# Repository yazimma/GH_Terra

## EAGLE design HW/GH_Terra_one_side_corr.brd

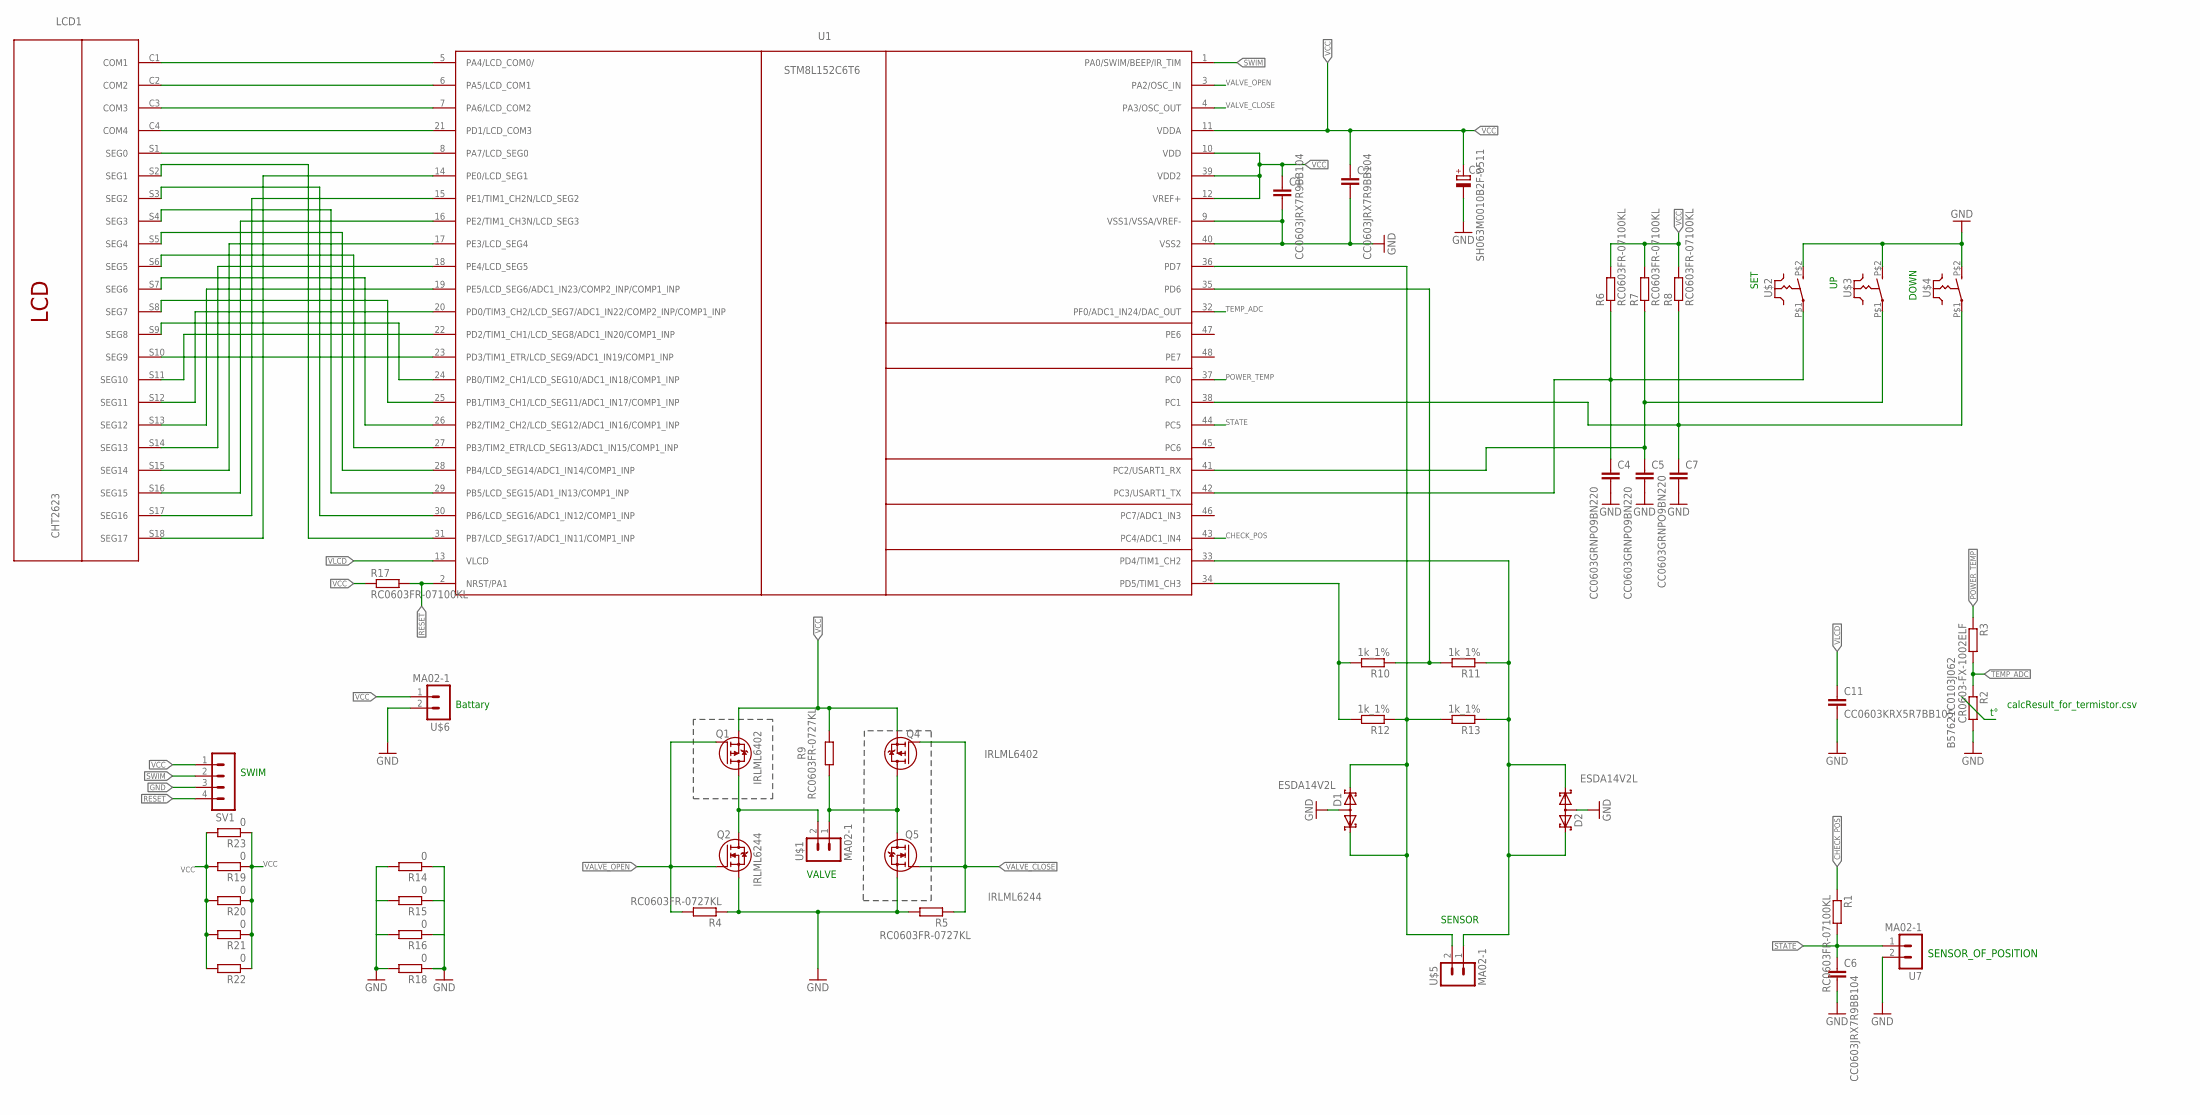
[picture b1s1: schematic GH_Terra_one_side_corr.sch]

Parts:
C1, C2, C6: CC0603JRX7R9BB104; C0603_IPC
C3: SH063M0010B2F-0511; SANYO-OSCON_C6
C4, C5, C7: CC0603GRNPO9BN220; C0603_IPC
C11: CC0603KRX5R7BB105; C0603_IPC
D1, D2: ESDA14V2L; SOT23
LCD1: CHT2623
Q1, Q4: IRLML6402; SOT23
Q2, Q5: IRLML6244; SOT23
R1, R6, R7, R8, R17: RC0603FR-07100KL; R0603_IPC
R2: B57621C0103J062; R1206
R3: CR0603-FX-1002ELF; R0603_IPC
R4, R5, R9: RC0603FR-0727KL; R0603_IPC
R10, R11, R12, R13: 1k_1%; R0603_IPC
R14, R15, R16, R18, R19, R20, R21, R22, R23: 0; R0603_IPC
SV1: MA04-1
U1: STM8L152C6T6; LQFP48
U7: MA02-1
U$1, U$5, U$6: MA02-1
U$2, U$3, U$4: RK_4X3; RK_3X4

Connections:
CHECK_POS: R1.1, U1.43 (PC4/ADC1_IN4)
GND: C1.2, C2.2, C3.-, C4.2, C5.2, C6.2, C7.2, C11.2, D1.3 (AA), D2.3 (AA), Q2.2 (S), Q5.2 (S), R2.2, R4.1, R5.2, R14.1, R14.2, R15.1, R15.2, R16.1, R16.2, R18.1, R18.2, SV1.3, U1.9 (VSS1/VSSA/VREF-), U1.40 (VSS2), U7.2, U$2.P$2 (S), U$3.P$2 (S), U$4.P$2 (S), U$6.2
unnamed: LCD1.C1 (COM1), U1.5 (PA4/LCD_COM0/)
unnamed: Q1.3 (D), Q2.3 (D), U$1.2
unnamed: Q4.3 (D), Q5.3 (D), R9.2, U$1.1
unnamed: LCD1.C2 (COM2), U1.6 (PA5/LCD_COM1)
unnamed: LCD1.C3 (COM3), U1.7 (PA6/LCD_COM2)
unnamed: LCD1.C4 (COM4), U1.21 (PD1/LCD_COM3)
unnamed: LCD1.S1 (SEG0), U1.8 (PA7/LCD_SEG0)
unnamed: LCD1.S17 (SEG16), U1.15 (PE1/TIM1_CH2N/LCD_SEG2)
unnamed: LCD1.S16 (SEG15), U1.16 (PE2/TIM1_CH3N/LCD_SEG3)
unnamed: LCD1.S15 (SEG14), U1.17 (PE3/LCD_SEG4)
unnamed: LCD1.S14 (SEG13), U1.18 (PE4/LCD_SEG5)
unnamed: LCD1.S13 (SEG12), U1.19 (PE5/LCD_SEG6/ADC1_IN23/COMP2_INP/COMP1_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)
unnamed: LCD1.S12 (SEG11), U1.20 (PD0/TIM3_CH2/LCD_SEG7/ADC1_IN22/COMP2_I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)
unnamed: LCD1.S11 (SEG10), U1.22 (PD2/TIM1_CH1/LCD_SEG8/ADC1_IN20/COMP1_I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)
unnamed: LCD1.S10 (SEG9), U1.23 (PD3/TIM1_ETR/LCD_SEG9/ADC1_IN19/COMP1_I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)
unnamed: LCD1.S9 (SEG8), U1.24 (PB0/TIM2_CH1/LCD_SEG10/ADC1_IN18/COMP1_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)
unnamed: LCD1.S8 (SEG7), U1.25 (PB1/TIM3_CH1/LCD_SEG11/ADC1_IN17/COMP1_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)
unnamed: LCD1.S7 (SEG6), U1.26 (PB2/TIM2_CH2/LCD_SEG12/ADC1_IN16/COMP1_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)
unnamed: LCD1.S6 (SEG5), U1.27 (PB3/TIM2_ETR/LCD_SEG13/ADC1_IN15/COMP1_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)
unnamed: LCD1.S5 (SEG4), U1.28 (PB4/LCD_SEG14/ADC1_IN14/COMP1_INP)
unnamed: LCD1.S4 (SEG3), U1.29 (PB5/LCD_SEG15/AD1_IN13/COMP1_INP)
unnamed: LCD1.S3 (SEG2), U1.30 (PB6/LCD_SEG16/ADC1_IN12/COMP1_INP)
unnamed: LCD1.S2 (SEG1), U1.31 (PB7/LCD_SEG17/ADC1_IN11/COMP1_INP)
unnamed: LCD1.S18 (SEG17), U1.14 (PE0/LCD_SEG1)
unnamed: D2.1 (K1), D2.2 (K2), R11.1, R13.1, U1.33 (PD4/TIM1_CH2), U$5.1
unnamed: R10.2, R12.2, U1.34 (PD5/TIM1_CH3)
unnamed: C4.1, R6.1, U1.42 (PC3/USART1_TX), U$2.P$1
unnamed: C5.1, R7.1, U1.41 (PC2/USART1_RX), U$3.P$1
unnamed: C7.1, R8.1, U1.38 (PC1), U$4.P$1
POWER_TEMP: R3.1, U1.37 (PC0)
RESET: R17.2, SV1.4, U1.2 (NRST/PA1)
STATE: C6.1, R1.2, U1.44 (PC5), U7.1
SWIM: SV1.2, U1.1 (PA0/SWIM/BEEP/IR_TIM)
TEMP_ADC: R2.1, R3.2, U1.32 (PF0/ADC1_IN24/DAC_OUT)
VALVE_CLOSE: Q4.1 (G), Q5.1 (G), R5.1, U1.4 (PA3/OSC_OUT)
VALVE_OPEN: Q1.1 (G), Q2.1 (G), R4.2, U1.3 (PA2/OSC_IN)
VCC: C1.1, C2.1, C3.+, Q1.2 (S), Q4.2 (S), R6.2, R7.2, R8.2, R9.1, R17.1, R19.1, R19.2, R20.1, R20.2, R21.1, R21.2, R22.1, R22.2, R23.1, R23.2, SV1.1, U1.10 (VDD), U1.11 (VDDA), U1.12 (VREF+), U1.39 (VDD2), U$6.1
VLCD: C11.1, U1.13 (VLCD)
VREF: R10.1, R11.2, U1.35 (PD6)
VREF1: D1.1 (K1), D1.2 (K2), R12.1, R13.2, U1.36 (PD7), U$5.2

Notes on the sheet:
calcResult_for_termistor.csv
Battary
SWIM
VALVE
SENSOR
SET
DOWN
SENSOR_OF_POSITION

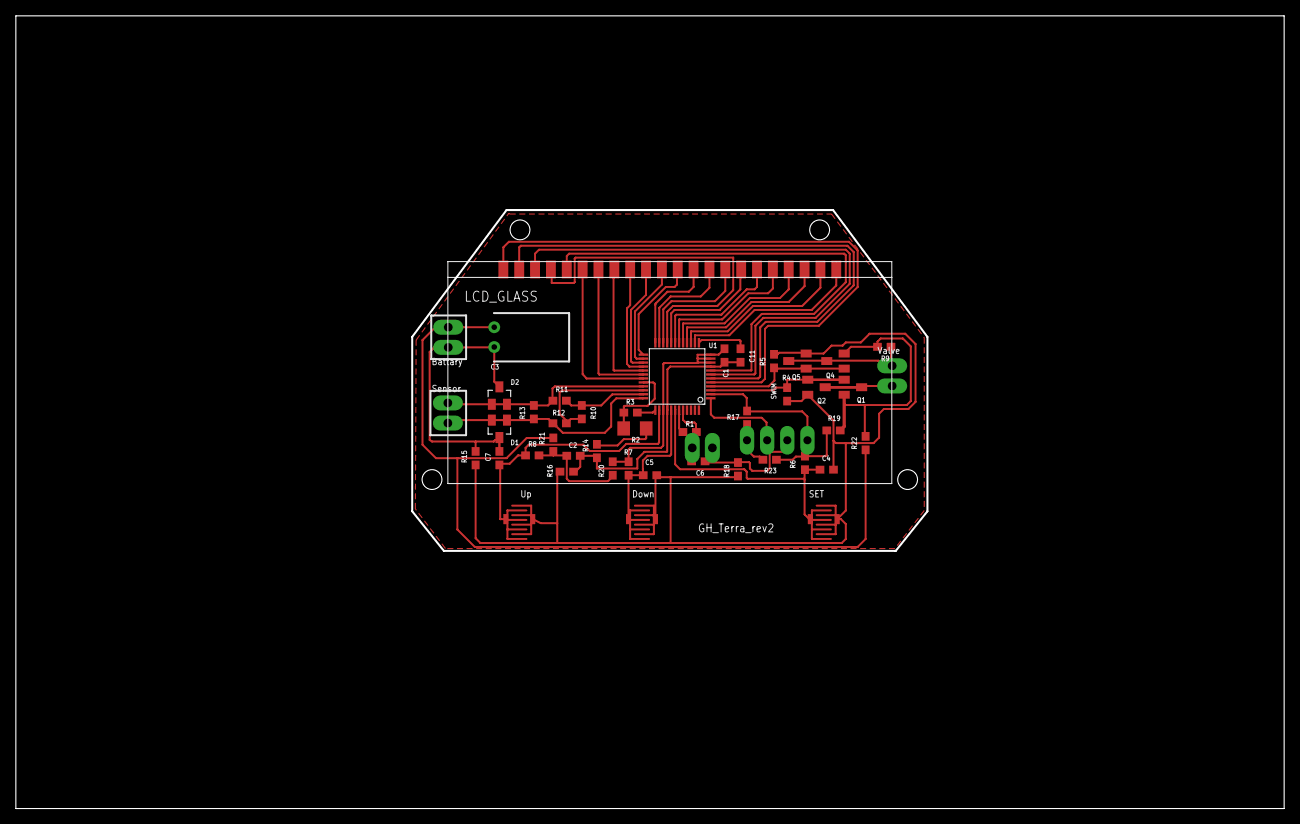
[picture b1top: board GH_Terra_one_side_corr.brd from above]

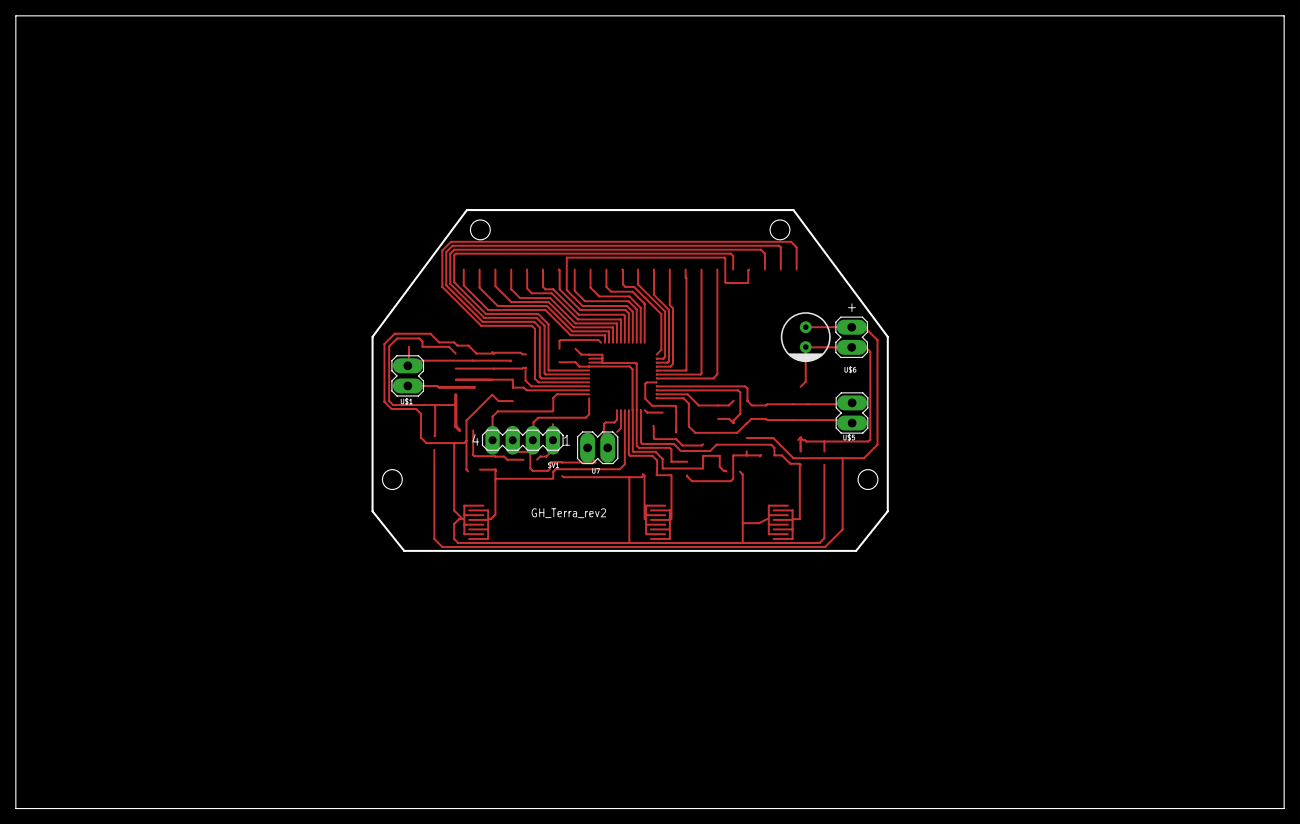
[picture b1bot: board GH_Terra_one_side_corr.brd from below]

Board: 2 copper layers, 160.0 x 100.0 mm, 47 parts (6 on the bottom side), 42 nets.

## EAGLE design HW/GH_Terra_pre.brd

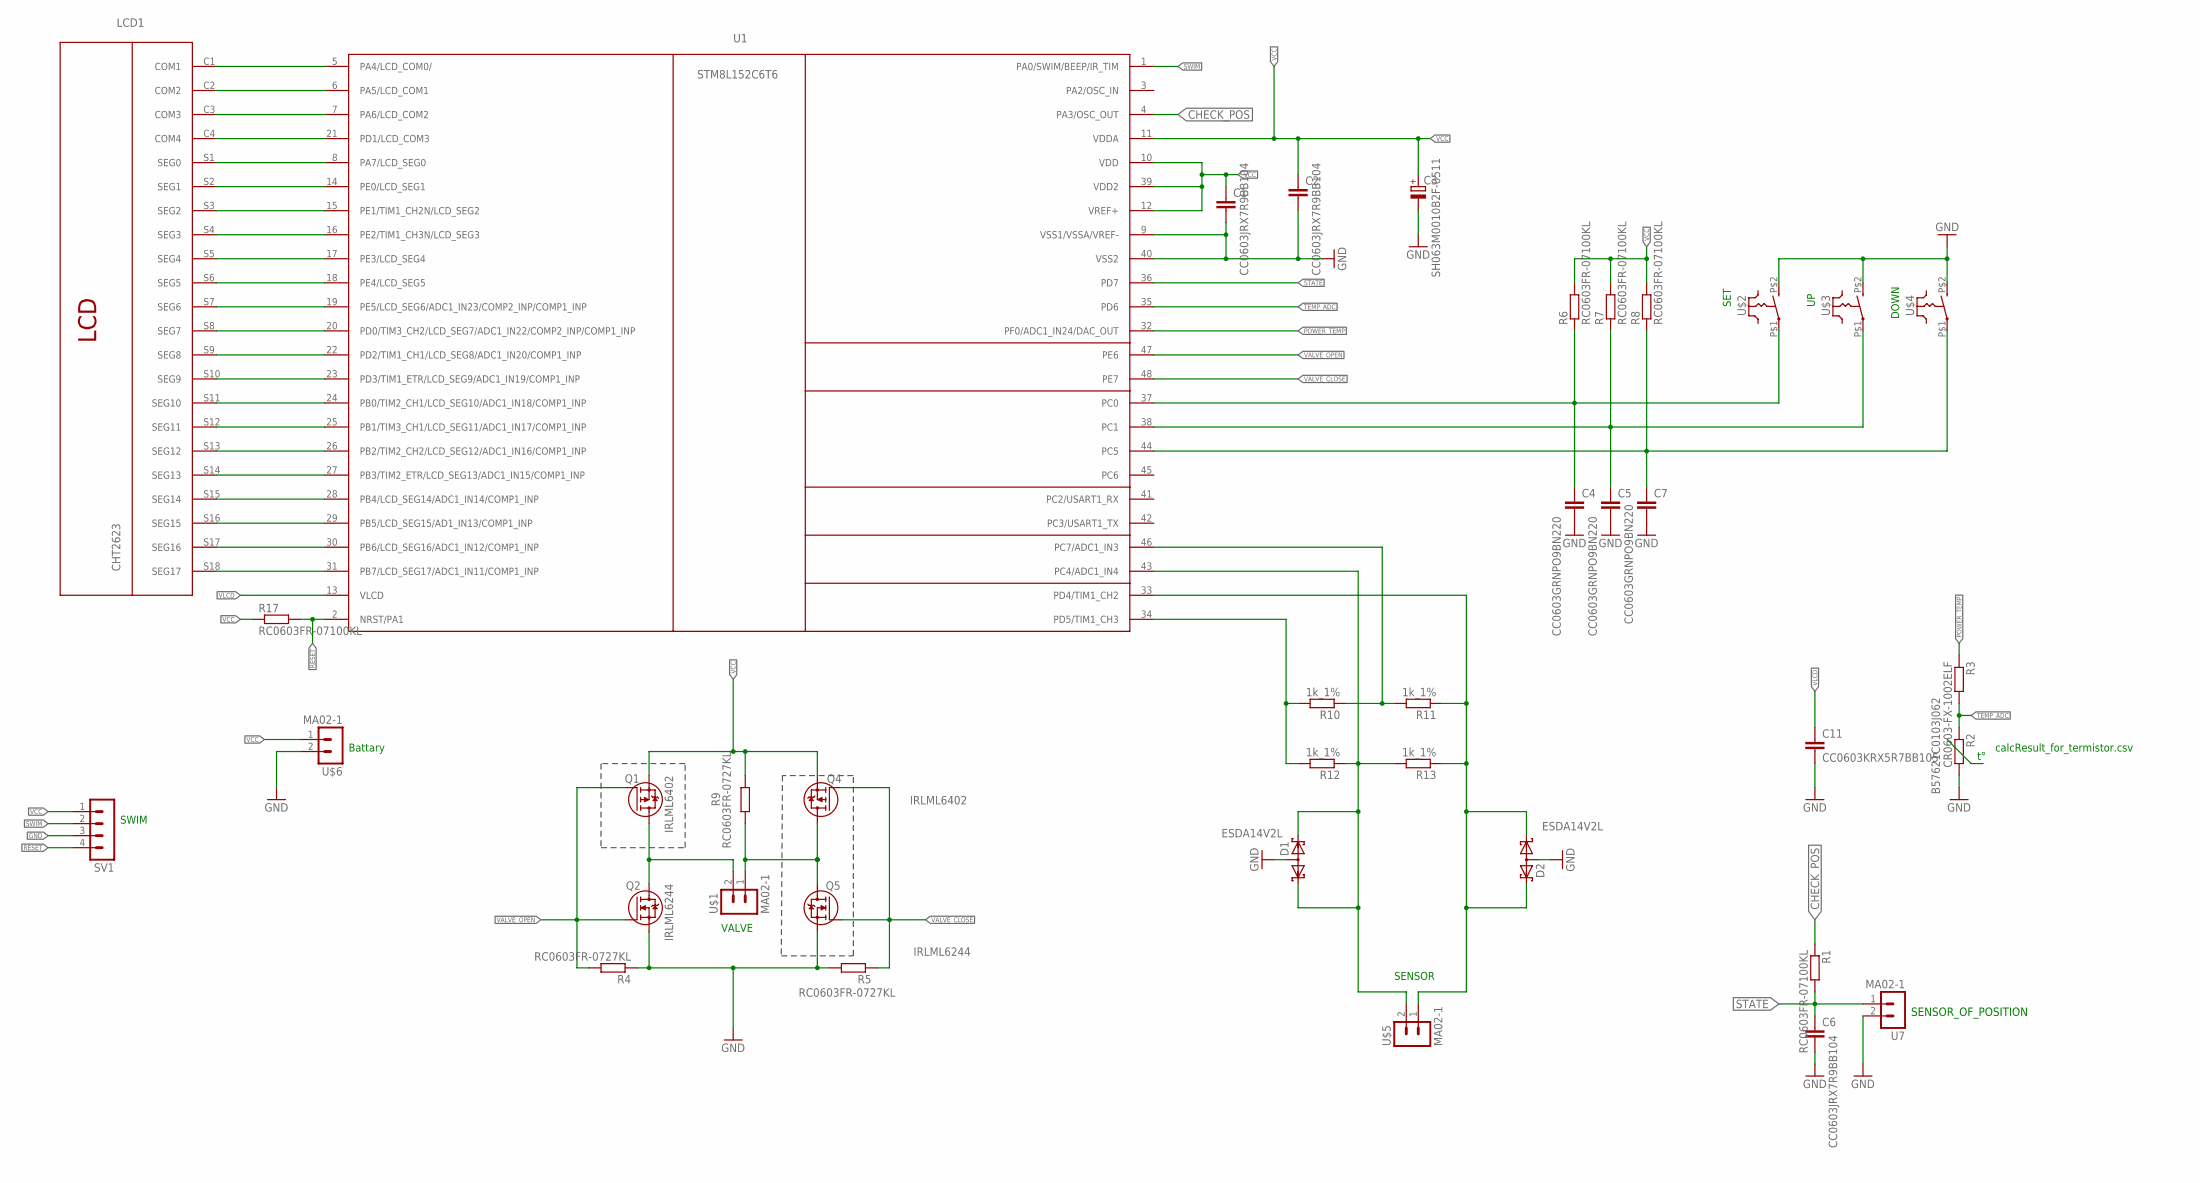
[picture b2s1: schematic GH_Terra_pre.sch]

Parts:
C1, C2, C6: CC0603JRX7R9BB104; C0603_IPC
C3: SH063M0010B2F-0511; SANYO-OSCON_C6
C4, C5, C7: CC0603GRNPO9BN220; C0603_IPC
C11: CC0603KRX5R7BB105; C0603_IPC
D1, D2: ESDA14V2L; SOT23
LCD1: CHT2623
Q1, Q4: IRLML6402; SOT23
Q2, Q5: IRLML6244; SOT23
R1, R6, R7, R8, R17: RC0603FR-07100KL; R0603_IPC
R2: B57621C0103J062; R1206
R3: CR0603-FX-1002ELF; R0603_IPC
R4, R5, R9: RC0603FR-0727KL; R0603_IPC
R10, R11, R12, R13: 1k_1%; R0603_IPC
SV1: MA04-1
U1: STM8L152C6T6; LQFP48
U7: MA02-1
U$1, U$5, U$6: MA02-1
U$2, U$3, U$4: RK_4X3; RK_3X4

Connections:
CHECK_POS: R1.1, U1.4 (PA3/OSC_OUT)
GND: C1.2, C2.2, C3.-, C4.2, C5.2, C6.2, C7.2, C11.2, D1.3 (AA), D2.3 (AA), Q2.2 (S), Q5.2 (S), R2.2, R4.1, R5.2, SV1.3, U1.9 (VSS1/VSSA/VREF-), U1.40 (VSS2), U7.2, U$2.P$2 (S), U$3.P$2 (S), U$4.P$2 (S), U$6.2
unnamed: Q1.3 (D), Q2.3 (D), U$1.2
unnamed: Q4.3 (D), Q5.3 (D), R9.2, U$1.1
unnamed: LCD1.C1 (COM1), U1.5 (PA4/LCD_COM0/)
unnamed: LCD1.C2 (COM2), U1.6 (PA5/LCD_COM1)
unnamed: LCD1.C3 (COM3), U1.7 (PA6/LCD_COM2)
unnamed: LCD1.C4 (COM4), U1.21 (PD1/LCD_COM3)
unnamed: LCD1.S1 (SEG0), U1.8 (PA7/LCD_SEG0)
unnamed: LCD1.S2 (SEG1), U1.14 (PE0/LCD_SEG1)
unnamed: LCD1.S3 (SEG2), U1.15 (PE1/TIM1_CH2N/LCD_SEG2)
unnamed: LCD1.S4 (SEG3), U1.16 (PE2/TIM1_CH3N/LCD_SEG3)
unnamed: LCD1.S5 (SEG4), U1.17 (PE3/LCD_SEG4)
unnamed: LCD1.S6 (SEG5), U1.18 (PE4/LCD_SEG5)
unnamed: LCD1.S7 (SEG6), U1.19 (PE5/LCD_SEG6/ADC1_IN23/COMP2_INP/COMP1_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)
unnamed: LCD1.S8 (SEG7), U1.20 (PD0/TIM3_CH2/LCD_SEG7/ADC1_IN22/COMP2_I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)
unnamed: LCD1.S9 (SEG8), U1.22 (PD2/TIM1_CH1/LCD_SEG8/ADC1_IN20/COMP1_I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)
unnamed: LCD1.S10 (SEG9), U1.23 (PD3/TIM1_ETR/LCD_SEG9/ADC1_IN19/COMP1_I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)
unnamed: LCD1.S11 (SEG10), U1.24 (PB0/TIM2_CH1/LCD_SEG10/ADC1_IN18/COMP1_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)
unnamed: LCD1.S12 (SEG11), U1.25 (PB1/TIM3_CH1/LCD_SEG11/ADC1_IN17/COMP1_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)
unnamed: LCD1.S13 (SEG12), U1.26 (PB2/TIM2_CH2/LCD_SEG12/ADC1_IN16/COMP1_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)
unnamed: LCD1.S14 (SEG13), U1.27 (PB3/TIM2_ETR/LCD_SEG13/ADC1_IN15/COMP1_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)
unnamed: LCD1.S15 (SEG14), U1.28 (PB4/LCD_SEG14/ADC1_IN14/COMP1_INP)
unnamed: LCD1.S16 (SEG15), U1.29 (PB5/LCD_SEG15/AD1_IN13/COMP1_INP)
unnamed: D2.1 (K1), D2.2 (K2), R11.1, R13.1, U1.33 (PD4/TIM1_CH2), U$5.1
unnamed: R10.2, R12.2, U1.34 (PD5/TIM1_CH3)
unnamed: LCD1.S17 (SEG16), U1.30 (PB6/LCD_SEG16/ADC1_IN12/COMP1_INP)
unnamed: C4.1, R6.1, U1.37 (PC0), U$2.P$1
unnamed: C5.1, R7.1, U1.38 (PC1), U$3.P$1
unnamed: C7.1, R8.1, U1.44 (PC5), U$4.P$1
unnamed: LCD1.S18 (SEG17), U1.31 (PB7/LCD_SEG17/ADC1_IN11/COMP1_INP)
POWER_TEMP: R3.1, U1.32 (PF0/ADC1_IN24/DAC_OUT)
RESET: R17.2, SV1.4, U1.2 (NRST/PA1)
STATE: C6.1, R1.2, U1.36 (PD7), U7.1
SWIM: SV1.2, U1.1 (PA0/SWIM/BEEP/IR_TIM)
TEMP_ADC: R2.1, R3.2, U1.35 (PD6)
VALVE_CLOSE: Q4.1 (G), Q5.1 (G), R5.1, U1.48 (PE7)
VALVE_OPEN: Q1.1 (G), Q2.1 (G), R4.2, U1.47 (PE6)
VCC: C1.1, C2.1, C3.+, Q1.2 (S), Q4.2 (S), R6.2, R7.2, R8.2, R9.1, R17.1, SV1.1, U1.10 (VDD), U1.11 (VDDA), U1.12 (VREF+), U1.39 (VDD2), U$6.1
VLCD: C11.1, U1.13 (VLCD)
VREF: R10.1, R11.2, U1.46 (PC7/ADC1_IN3)
VREF1: D1.1 (K1), D1.2 (K2), R12.1, R13.2, U1.43 (PC4/ADC1_IN4), U$5.2

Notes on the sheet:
calcResult_for_termistor.csv
Battary
SWIM
VALVE
SENSOR
SET
DOWN
SENSOR_OF_POSITION

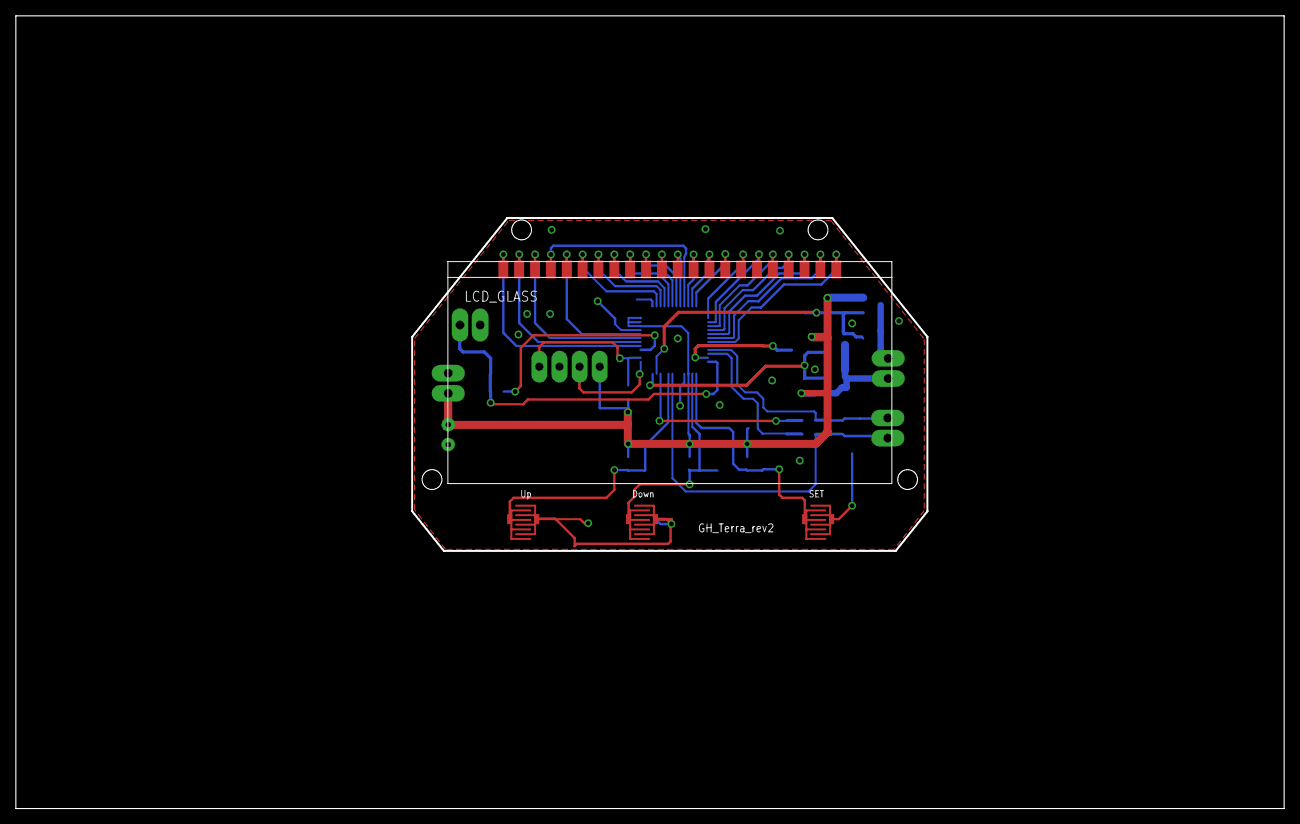
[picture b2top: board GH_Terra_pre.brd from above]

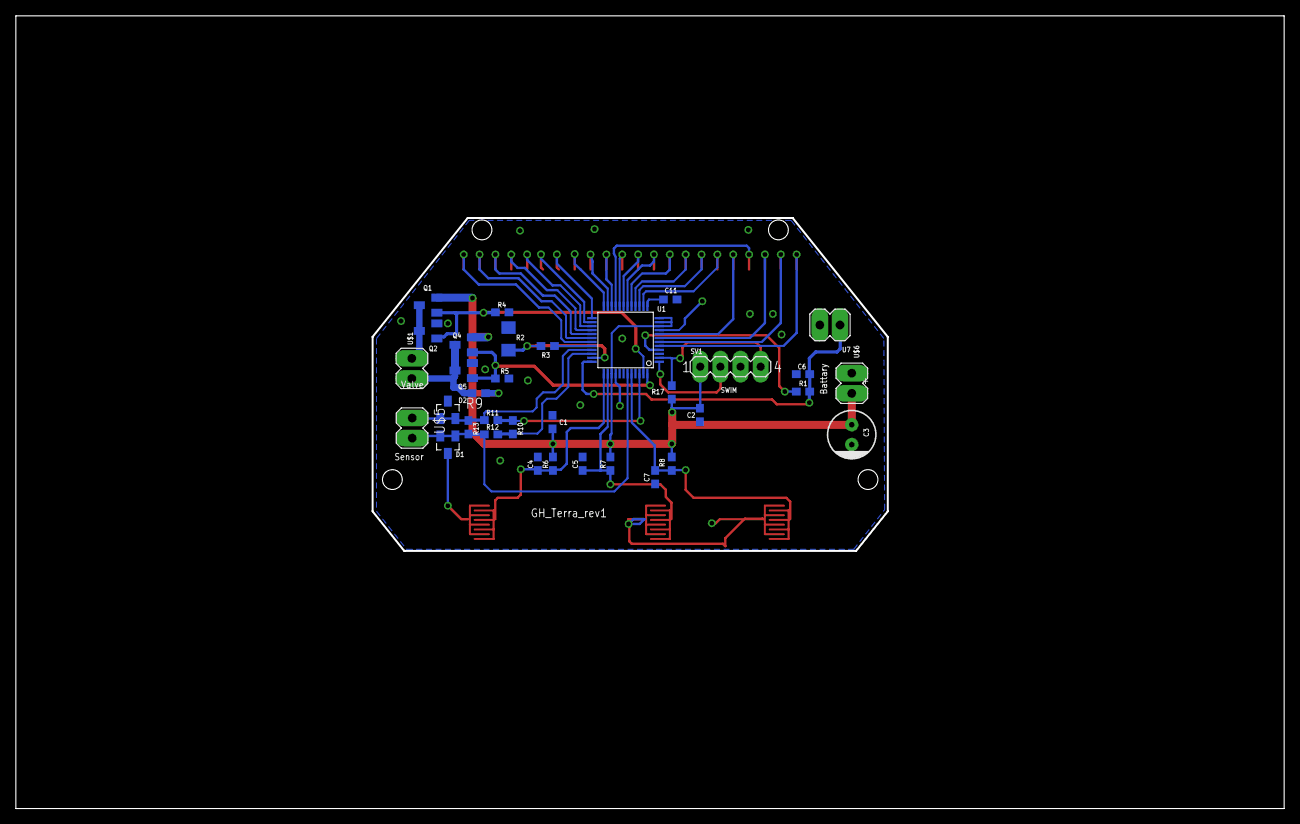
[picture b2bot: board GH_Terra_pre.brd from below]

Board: 2 copper layers, 160.0 x 100.0 mm, 38 parts (34 on the bottom side), 42 nets.

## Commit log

2014-10-30 Мастер коммит
2014-11-02 Первая ревизия готовой тестовой программы для отработки метода измерения.
2014-12-20 Почти полная версия.
2014-12-25 Решены все замечания. Добавлено сохранение рабочих переменных в энергонезависимой памяти. Добавлено сервисное меню в нем можно установить поправку нулевой точки моста и температуру блокировки.
2014-12-30 бЕТТА ВЕРСИЯ. Согласно ТЗ. С Новым Годом.
2015-01-18 Энергосбережение
2015-01-18 REV1
2015-02-28 Закостылили мерцание показаний датчика влажности. Гореть мне в Аду за это....
2015-03-04 Введено: Защитный интервал между поливами. В сервисное меню добавлена настройка защитного интервала
2015-03-04 Обдумал... И задал себе вопрос А что если кран рассинхронизируется? Нужно безусловно определять положение!!!
2015-03-04 Ветка с клапаном в виде моторчика и пневмогидравлического клапана
2015-03-12 Допилен автомат управления мотором и добавлена хитрушка. Отправлено заказчику.
2015-03-30 Более стабильная версия.
2015-08-17 Версия для односторонней платой. Первая редакция. Перенастроены порты и проверены все основные функции
2015-10-27 Корректировки от заказчика в первом приближении
2015-11-22 Переписан автомат моторчика
2015-12-06 Фиксация перед приведением в соответствии с инструкцией
2015-12-15 доработки к инструкции
2015-12-21 Закончил противоугонку
2016-01-06 Добрался до показаний в режиме низкой температуры
2016-01-08 Закончено приведение к инструкции. Готово к передаче заказчику
2016-01-09 Разберемся с температурой
2016-01-09 Используем встроенный датчик температуры.
2016-01-11 Добавил гистерезис на блокировку по температуре
